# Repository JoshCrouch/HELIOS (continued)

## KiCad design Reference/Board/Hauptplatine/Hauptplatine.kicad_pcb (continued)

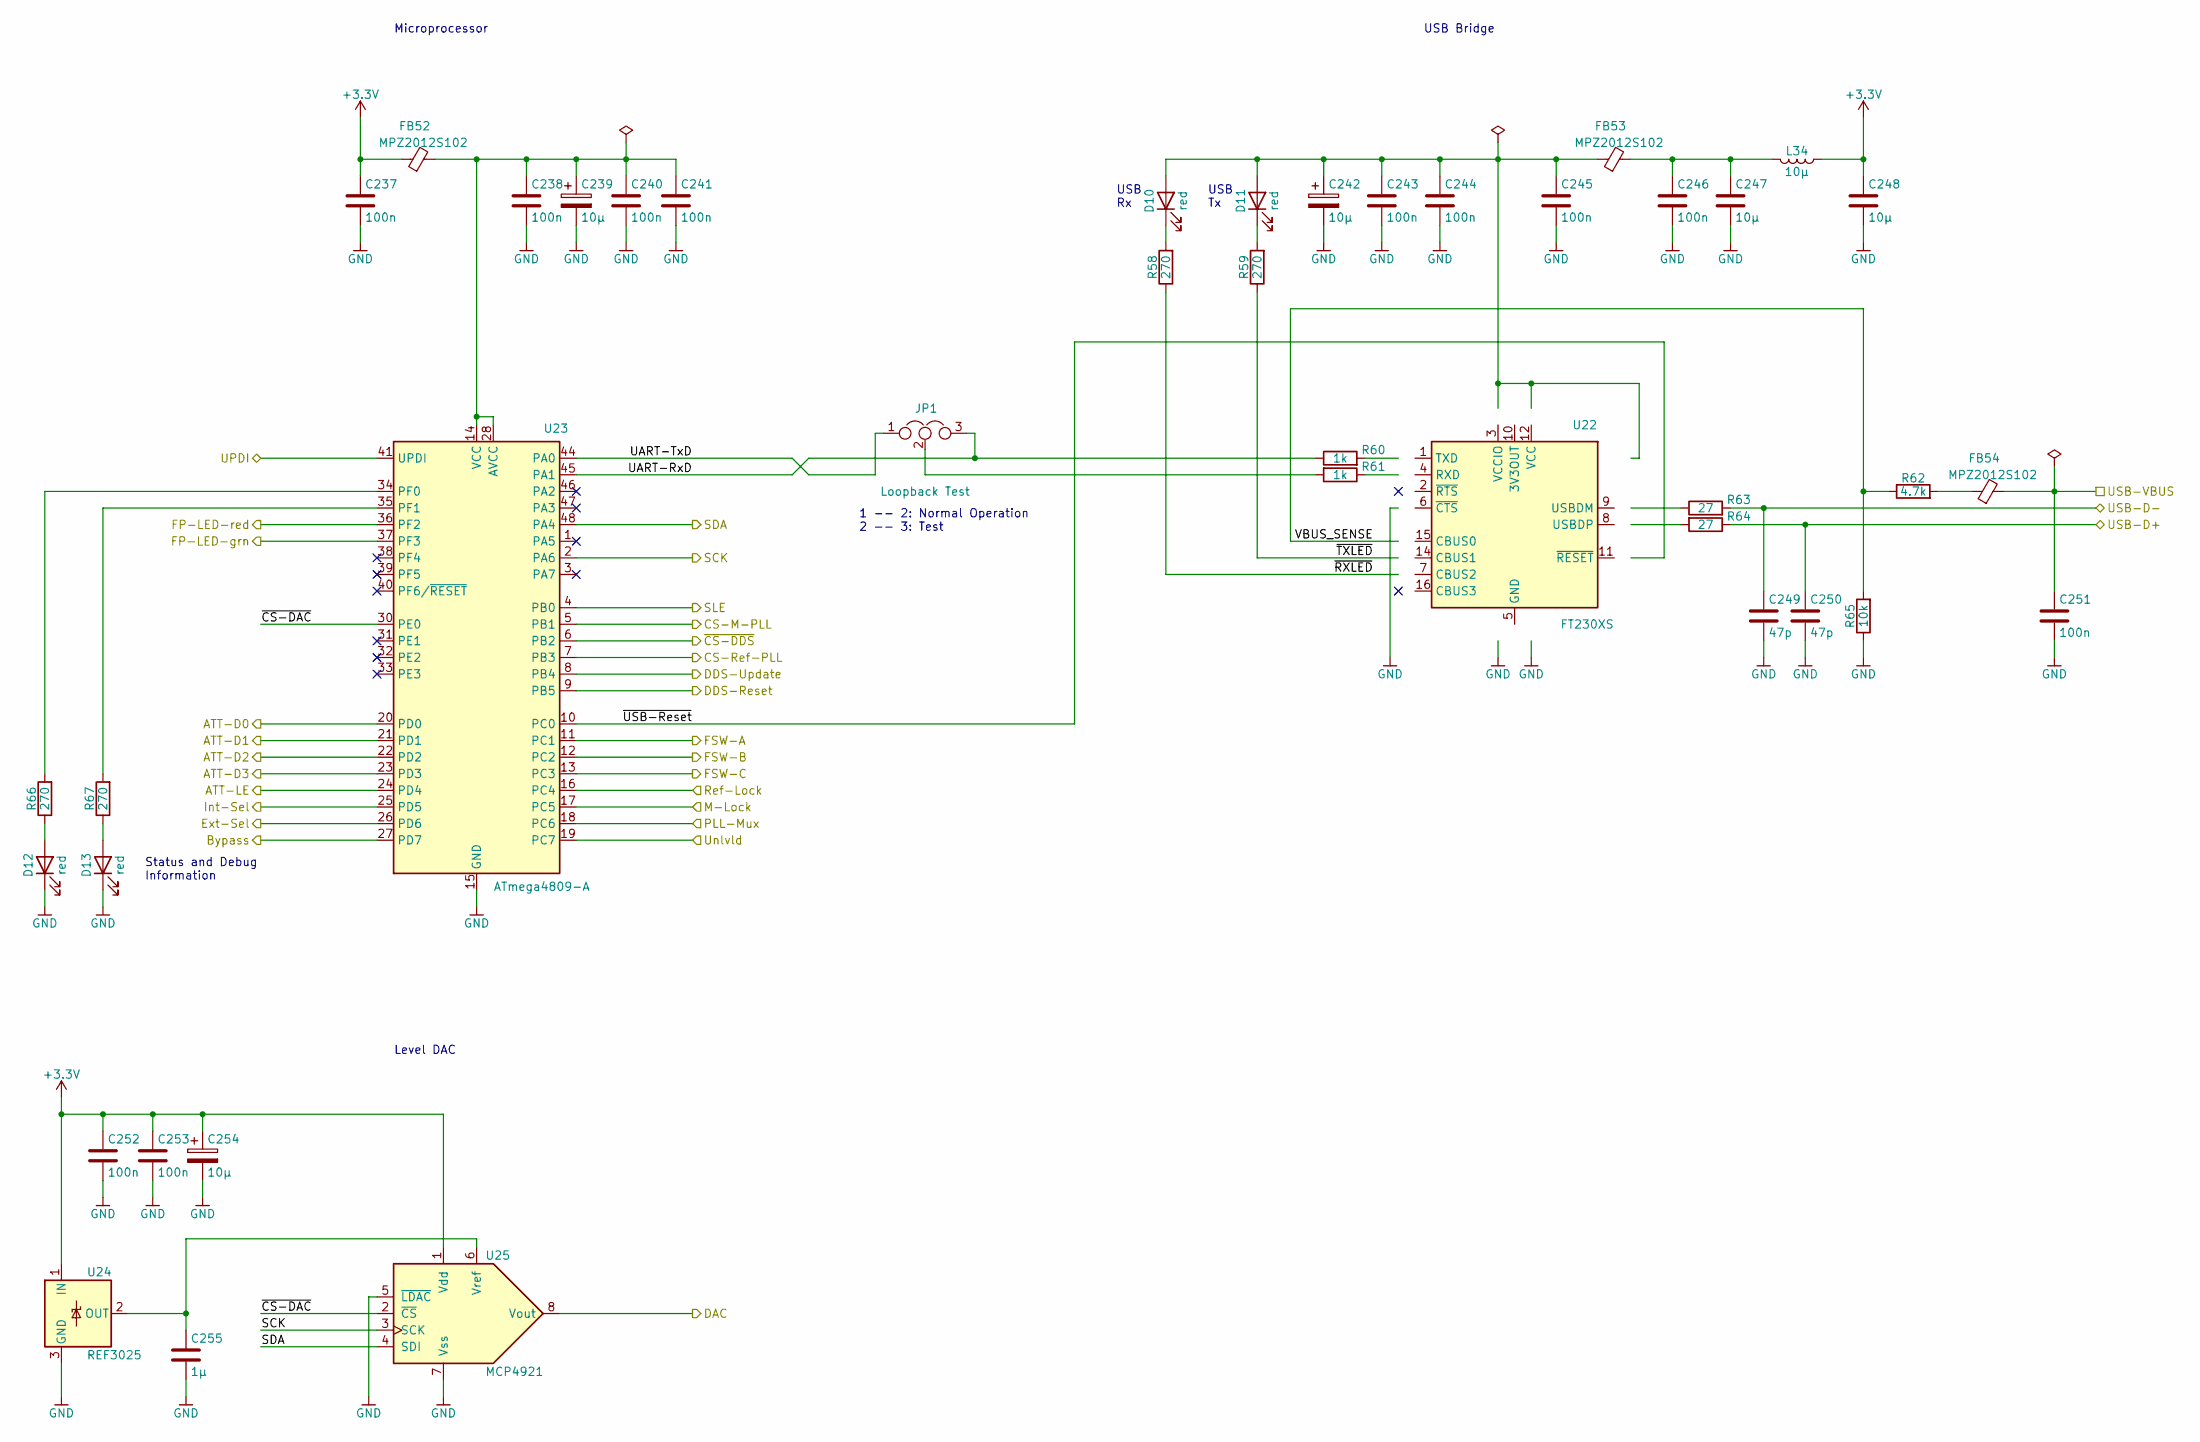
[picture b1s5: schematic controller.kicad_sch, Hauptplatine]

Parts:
C237, C238, C243, C244, C245, C246, C251, C252, C253: 100n; C_0805_2012Metric
C239, C242, C254: 10µ; CP_EIA-3528-21_Kemet-B
C240, C241: 100n; C_0603_1608Metric
C247, C248: 10µ; C_0805_2012Metric
C249, C250: 47p; C_0805_2012Metric
C255: 1µ; C_0805_2012Metric
D10, D11, D12, D13: red; LED_0805_2012Metric
FB52, FB53, FB54: MPZ2012S102; L_0805_2012Metric
JP1: Jumper-3; PinHeader_1x03_P2.54mm_Vertical
L34: 10µ; L_0805_2012Metric
R58, R59, R66, R67: 270; R_0805_2012Metric
R60, R61: 1k; R_0805_2012Metric
R62: 4.7k; R_0805_2012Metric
R63, R64: 27; R_0805_2012Metric
R65: 10k; R_0805_2012Metric
U22: FT230XS; SSOP-16_3.9x4.9mm_P0.635mm
U23: ATmega4809-A; TQFP-48_7x7mm_P0.5mm
U24: REF3025; SOT-23
U25: MCP4921; SOIC-8_3.9x4.9mm_P1.27mm

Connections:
/ATT-D0: U23.20 (PD0); also elsewhere on the board
/ATT-D1: U23.21 (PD1); also elsewhere on the board
/ATT-D2: U23.22 (PD2); also elsewhere on the board
/ATT-D3: U23.23 (PD3); also elsewhere on the board
/ATT-LE: U23.24 (PD4); also elsewhere on the board
/Bypass: U23.27 (PD7); also elsewhere on the board
/CS-M-PLL: U23.5 (PB1); also elsewhere on the board
/CS-Ref-PLL: U23.7 (PB3); also elsewhere on the board
/Controller/DAC: U25.8 (Vout); also elsewhere on the board
/Controller/FP-LED-grn: U23.37 (PF3); also elsewhere on the board
/Controller/FP-LED-red: U23.36 (PF2); also elsewhere on the board
/Controller/UART-RxD: JP1.3, R60.1, U23.45 (PA1)
/Controller/UART-TxD: JP1.1, U23.44 (PA0)
/Controller/UPDI: U23.41 (UPDI); also elsewhere on the board
/Controller/USB-D+: C250.1, R64.1; also elsewhere on the board
/Controller/USB-D-: C249.1, R63.2; also elsewhere on the board
/Controller/USB-VBUS: C251.1, FB54.2; also elsewhere on the board
/Controller/VBUS_SENSE: R62.1, R65.2, U22.15 (CBUS0)
/Controller/~CS-DAC: U23.30 (PE0), U25.2 (~CS)
/Controller/~RXLED: R58.1, U22.7 (CBUS2)
/Controller/~TXLED: R59.1, U22.14 (CBUS1)
/Controller/~USB-Reset: U22.11 (~RESET), U23.10 (PC0)
/DDS-Reset: U23.9 (PB5); also elsewhere on the board
/DDS-Update: U23.8 (PB4); also elsewhere on the board
/Ext-Sel: U23.26 (PD6); also elsewhere on the board
/FSW-A: U23.11 (PC1); also elsewhere on the board
/FSW-B: U23.12 (PC2); also elsewhere on the board
/FSW-C: U23.13 (PC3); also elsewhere on the board
/Int-Sel: U23.25 (PD5); also elsewhere on the board
/M-Lock: U23.17 (PC5); also elsewhere on the board
/PLL-Mux: U23.18 (PC6); also elsewhere on the board
/Ref-Lock: U23.16 (PC4); also elsewhere on the board
/SCK: U23.2 (PA6), U25.3 (SCK); also elsewhere on the board
/SDA: U23.48 (PA4), U25.4 (SDI); also elsewhere on the board
/SLE: U23.4 (PB0); also elsewhere on the board
/Unlvld: U23.19 (PC7); also elsewhere on the board
/~CS-DDS: U23.6 (PB2); also elsewhere on the board
unnamed: C238.1, C239.1, C240.1, C241.1, FB52.2, U23.14 (VCC), U23.28 (AVCC), U23.42 (VCC)
unnamed: C246.1, C247.1, FB53.2, L34.2
unnamed: C255.1, U24.2 (OUT), U25.6 (Vref)
unnamed: D10.1 (K), R58.2
unnamed: D11.1 (K), R59.2
unnamed: D12.2 (A), R66.1
unnamed: D13.2 (A), R67.1
unnamed: FB54.1, R62.2
unnamed: JP1.2, R61.2
unnamed: R60.2, U22.1 (TXD)
unnamed: R61.1, U22.4 (RXD)
unnamed: R63.1, U22.9 (USBDM)
unnamed: R64.2, U22.8 (USBDP)
unnamed: R66.2, U23.34 (PF0)
unnamed: R67.2, U23.35 (PF1)

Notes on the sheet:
1 -- 2: Normal Operation 2 -- 3: Test
Level DAC
Status and Debug Information
USB Tx
USB Rx
USB Bridge
Microprocessor

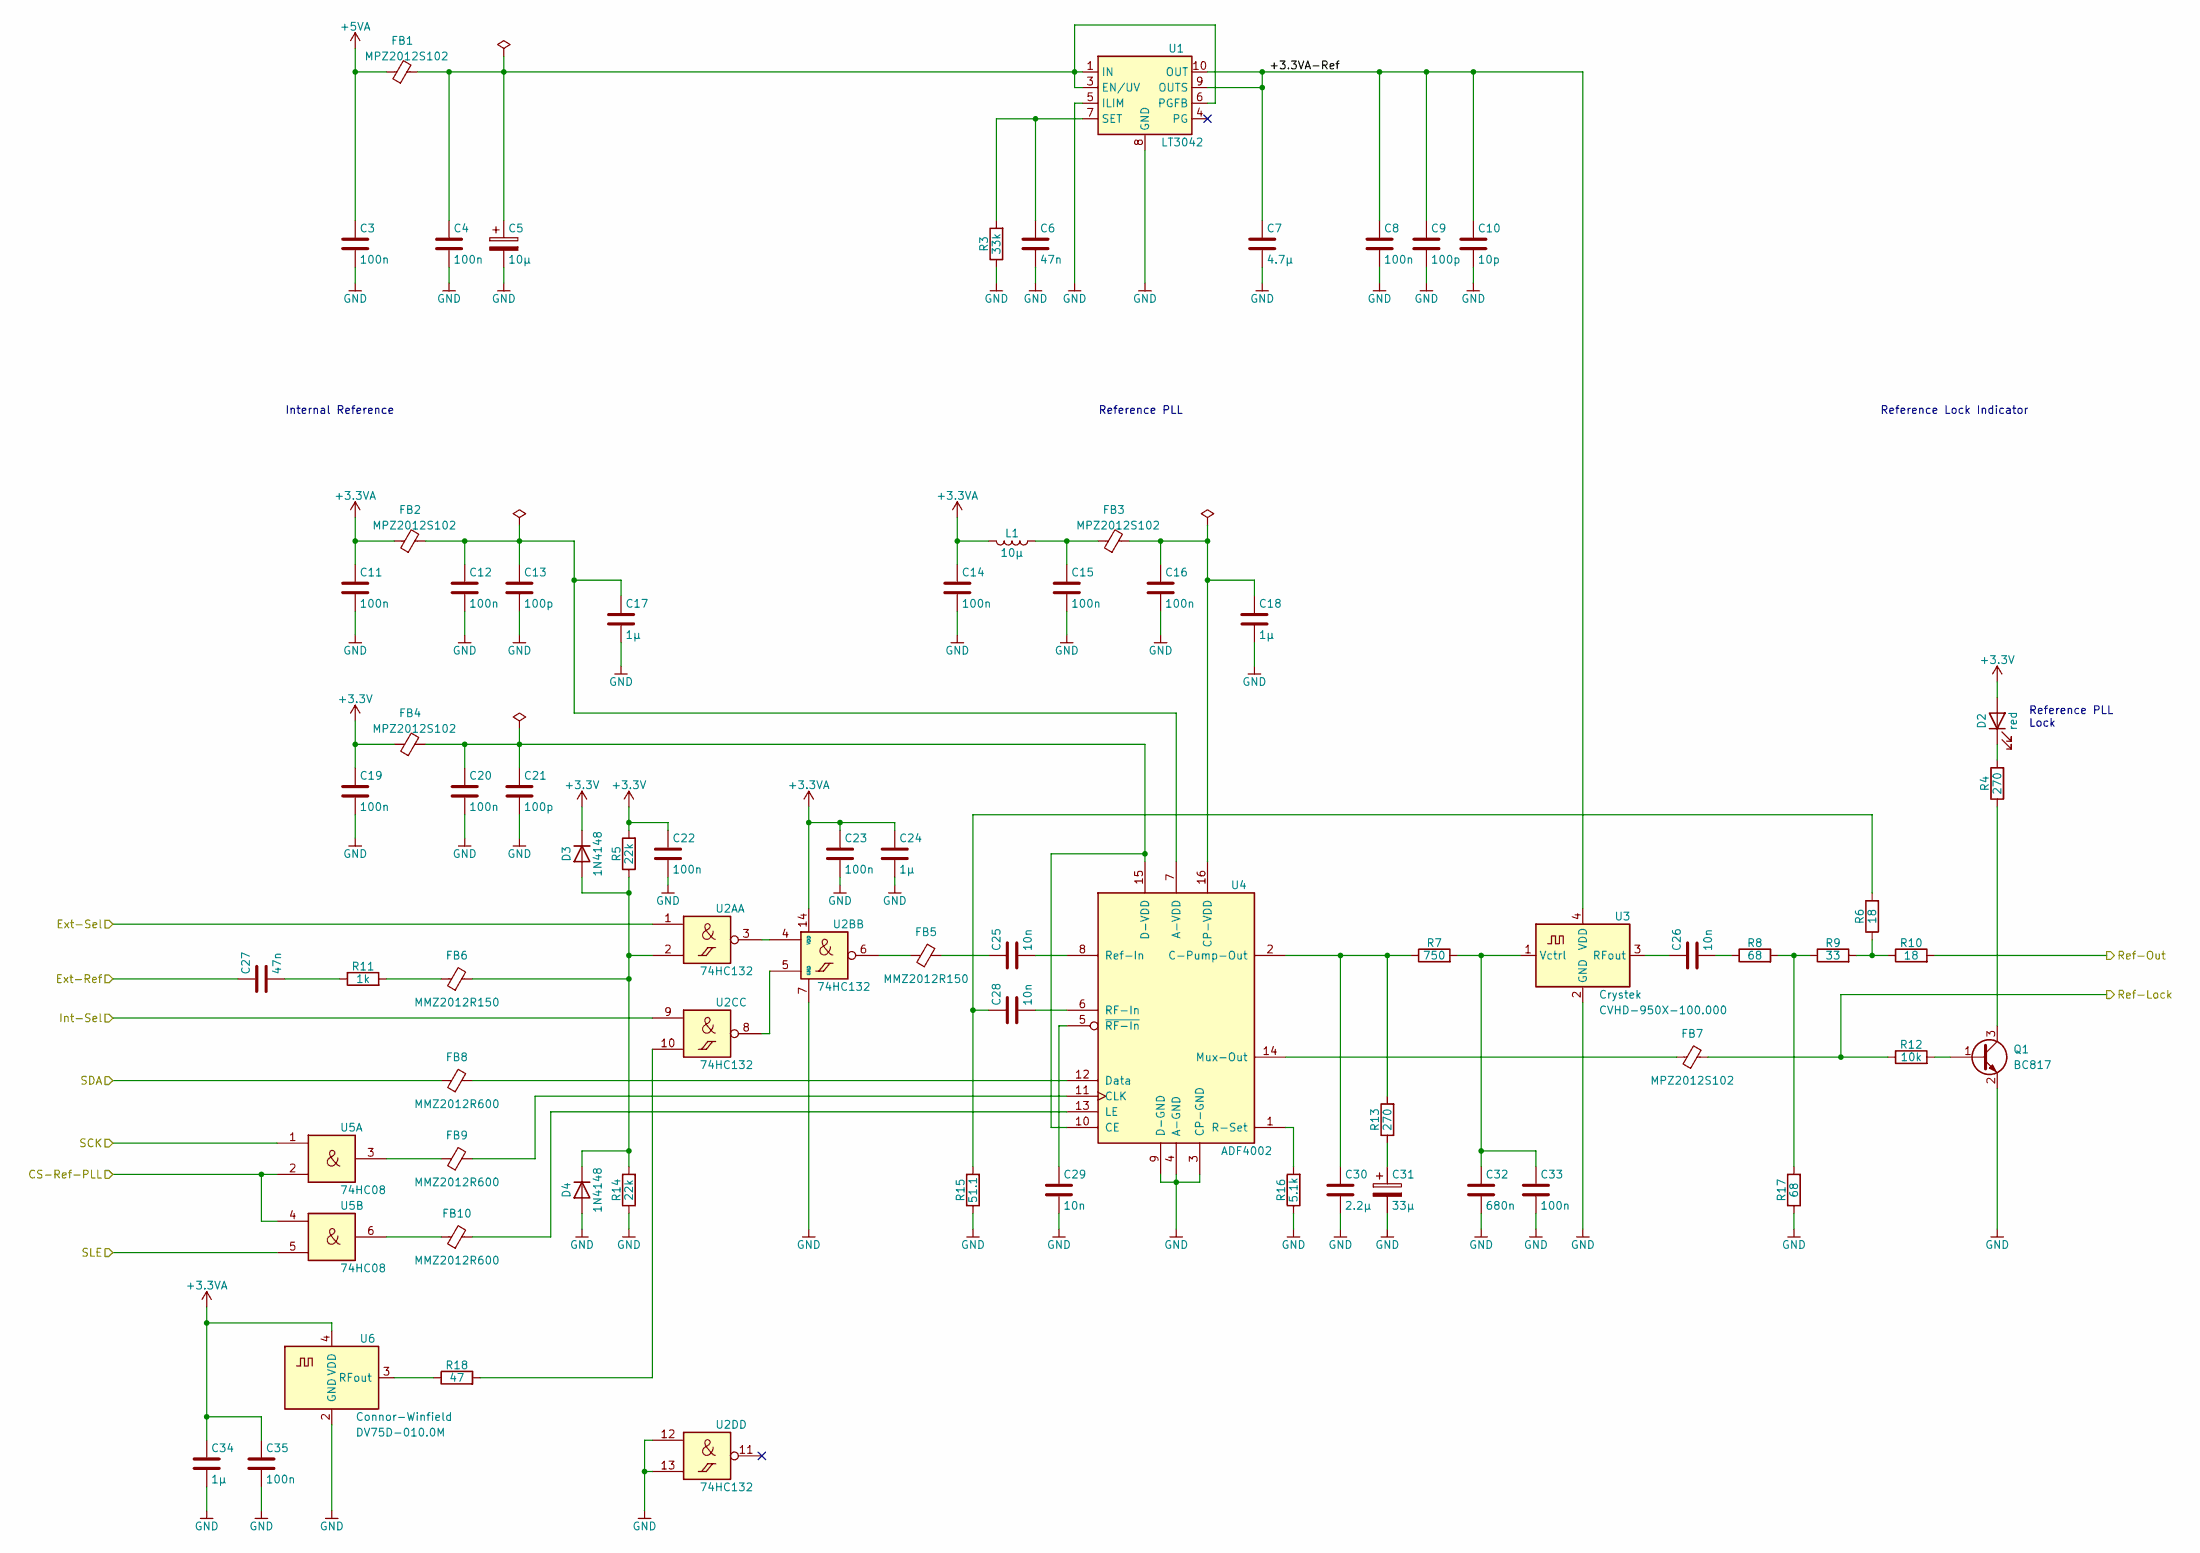
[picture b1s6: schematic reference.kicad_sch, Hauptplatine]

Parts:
C3, C4, C8, C11, C12, C14, C15, C16, C19, C20, C22, C23, C33, C35: 100n; C_0805_2012Metric
C5: 10µ; CP_EIA-3528-21_Kemet-B
C6, C27: 47n; C_0805_2012Metric
C7: 4.7µ; C_0805_2012Metric
C9, C13, C21: 100p; C_0805_2012Metric
C10: 10p; C_0805_2012Metric
C17, C18, C24, C34: 1µ; C_0805_2012Metric
C25, C26, C28, C29: 10n; C_0805_2012Metric
C30: 2.2µ; C_0805_2012Metric
C31: 33µ; CP_Radial_D5.0mm_P2.00mm
C32: 680n; C_0805_2012Metric
D2: red; LED_0805_2012Metric
D3, D4: 1N4148; D_SOD-323F
FB1, FB2, FB3, FB4, FB7: MPZ2012S102; L_0805_2012Metric
FB5, FB6: MMZ2012R150; L_0805_2012Metric
FB8, FB9, FB10: MMZ2012R600; L_0805_2012Metric
L1: 10µ; L_0805_2012Metric
Q1: BC817; SOT-23
R3: 33k; R_0805_2012Metric
R4, R13: 270; R_0805_2012Metric
R5, R14: 22k; R_0805_2012Metric
R6, R10: 18; R_0805_2012Metric
R7: 750; R_0805_2012Metric
R8, R17: 68; R_0805_2012Metric
R9: 33; R_0805_2012Metric
R11: 1k; R_0805_2012Metric
R12: 10k; R_0805_2012Metric
R15: 51.1; R_0805_2012Metric
R16: 5.1k; R_0805_2012Metric
R18: 47; R_0805_2012Metric
U1: LT3042; MSOP-10-1EP_3x3mm_P0.5mm_EP1.68x1.88mm
U2A, U2B, U2C, U2D, U2E: 74HC132; SOIC-14_3.9x8.7mm_P1.27mm
U3: CVHD-950X-100.000; VCXO_CVHD950_Crystek
U4: ADF4002; TSSOP-16_4.4x5mm_P0.65mm
U5: 74HC08; SOIC-14_3.9x8.7mm_P1.27mm
U6: DV75D-010.0M; DV75D_Oscillator_Connor-Winfield

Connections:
+3.3VA: C11.1, C14.1, C23.1, C24.1, C34.1, C35.1, FB2.1, L1.2, U2E.14 (VDD), U6.4 (VDD); also elsewhere on the board
+5VA: C3.1, FB1.1; also elsewhere on the board
/CS-Ref-PLL: U5.2, U5.4; also elsewhere on the board
/PLL and DDS/Ref-In: R10.2; also elsewhere on the board
/Ref-Lock: FB7.2, R12.1; also elsewhere on the board
/Reference/+3.3VA-Ref: C7.1, C8.1, C9.1, C10.1, U1.9 (OUTS), U1.10 (OUT), U3.4 (VDD)
/Reference/Ext-Ref: C27.1; also elsewhere on the board
/SCK: U5.1; also elsewhere on the board
/SDA: FB8.1; also elsewhere on the board
/SLE: U5.5; also elsewhere on the board
unnamed: C4.1, C5.1, FB1.2, U1.1 (IN), U1.2 (IN), U1.3 (EN/UV), U1.6 (PGFB)
unnamed: C6.1, R3.2, U1.7 (SET)
unnamed: C12.1, C13.1, C17.1, FB2.2, U4.7 (A-VDD)
unnamed: C15.1, FB3.1, L1.1
unnamed: C16.1, C18.1, FB3.2, U4.16 (CP-VDD)
unnamed: C20.1, C21.1, FB4.2, U4.10 (CE), U4.15 (D-VDD)
unnamed: C25.1, FB5.2
unnamed: C25.2, U4.8 (Ref-In)
unnamed: C26.1, U3.3 (RFout)
unnamed: C26.2, R8.1
unnamed: C27.2, R11.1
unnamed: C28.1, R6.2, R15.2
unnamed: C28.2, U4.6 (RF-In)
unnamed: C29.1, U4.5 (~RF-In)
unnamed: C30.1, R7.1, R13.2, U4.2 (C-Pump-Out)
unnamed: C31.1, R13.1
unnamed: C32.1, C33.1, R7.2, U3.1 (Vctrl)
unnamed: D2.1 (K), R4.2
unnamed 202: D3.2 (A), D4.1 (K), FB6.2, R5.1, R14.2, U2A.2; also elsewhere on the board
unnamed 215: FB5.1, U2B.6; also elsewhere on the board
unnamed: FB6.1, R11.2
unnamed: FB7.1, U4.14 (Mux-Out)
unnamed: FB8.2, U4.12 (Data)
unnamed: FB9.1, U5.3
unnamed: FB9.2, U4.11 (CLK)
unnamed: FB10.1, U5.6
unnamed: FB10.2, U4.13 (LE)
unnamed: Q1.1 (B), R12.2
unnamed: Q1.3 (C), R4.1
unnamed: R6.1, R9.2, R10.1
unnamed: R16.2, U4.1 (R-Set)
unnamed: R8.2, R9.1, R17.2
unnamed: R18.1, U6.3 (RFout)
unnamed 254: R18.2, U2C.10; also elsewhere on the board
unnamed: U2A.3, U2B.4
unnamed: U2B.5, U2C.8

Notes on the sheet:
Reference PLL
Reference Lock Indicator
Internal Reference
Reference PLL Lock

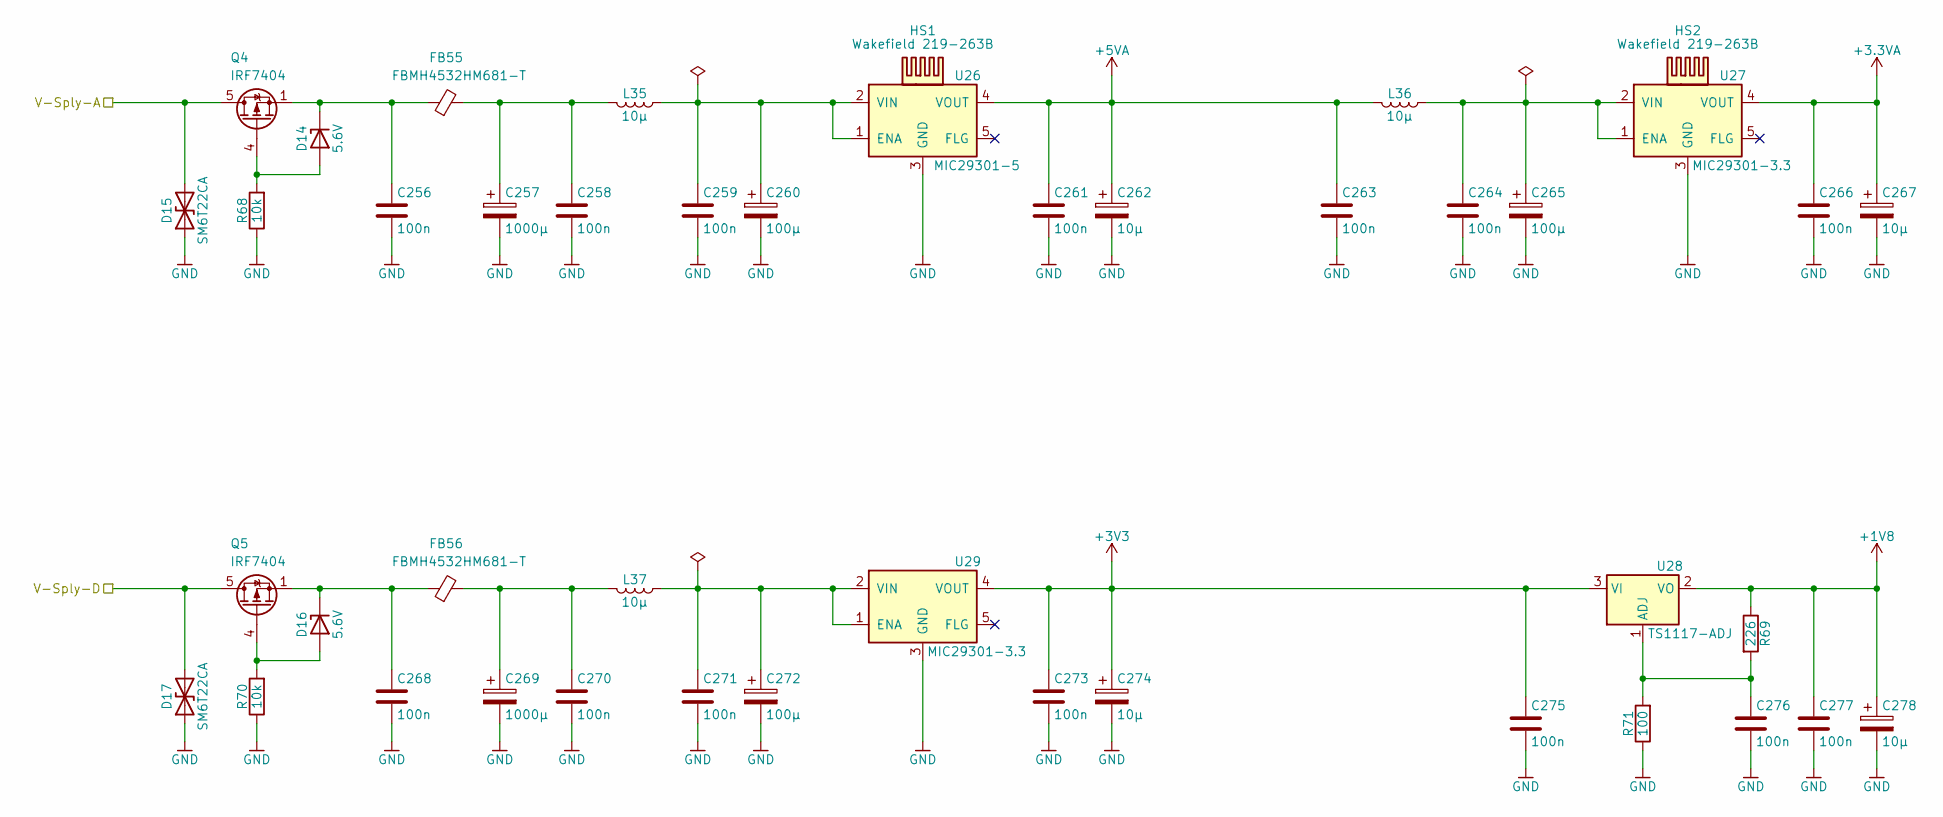
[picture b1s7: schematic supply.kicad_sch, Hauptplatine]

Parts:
C256, C258, C259, C261, C263, C264, C266, C268, C270, C271, C273, C275, C276, C277: 100n; C_0805_2012Metric
C257, C269: 1000µ; CP_Radial_D10.0mm_P5.00mm
C260, C265, C272: 100µ; CP_Radial_D6.3mm_P2.50mm
C262, C267, C274, C278: 10µ; CP_Radial_D5.0mm_P2.00mm
D14, D16: 5.6V; D_SOD-123
D15, D17: SM6T22CA; D_SMB
FB55, FB56: FBMH4532HM681-T; L_1812_4532Metric
HS1, HS2: Wakefield 219-263B; Heatsink-TO263_219-263B-TR_Wakefield
L35, L37: 10µ; L_Wuerth_WE-PD-Typ-LS
L36: 10µ; Wuerth_WE-TPC_Shielded
Q4, Q5: IRF7404; SOIC-8_3.9x4.9mm_P1.27mm
R68, R70: 10k; R_0805_2012Metric
R69: 226; R_0805_2012Metric
R71: 100; R_0805_2012Metric
U26: MIC29301-5; TO-263-5_TabPin3
U27, U29: MIC29301-3.3; TO-263-5_TabPin3
U28: TS1117-ADJ; TO-252-3_TabPin2

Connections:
+1V8: C277.1, C278.1, R69.1, U28.2 (VO); also elsewhere on the board
+3.3VA: C266.1, C267.1, U27.4 (VOUT); also elsewhere on the board
+5VA: C261.1, C262.1, C263.1, L36.2, U26.4 (VOUT); also elsewhere on the board
/Power Supply/V-Sply-A: D15.2 (A2), D17.2 (A2), Q4.5 (D), Q4.6 (D), Q4.7 (D), Q4.8 (D), Q5.5 (D), Q5.6 (D), Q5.7 (D), Q5.8 (D); also elsewhere on the board
unnamed: C256.1, D14.1 (K), FB55.1, Q4.1 (S), Q4.2 (S), Q4.3 (S)
unnamed: C257.1, C258.1, FB55.2, L35.2
unnamed: C259.1, C260.1, L35.1, U26.1 (ENA), U26.2 (VIN)
unnamed: C264.1, C265.1, L36.1, U27.1 (ENA), U27.2 (VIN)
unnamed: C268.1, D16.1 (K), FB56.1, Q5.1 (S), Q5.2 (S), Q5.3 (S)
unnamed: C269.1, C270.1, FB56.2, L37.2
unnamed: C271.1, C272.1, L37.1, U29.1 (ENA), U29.2 (VIN)
unnamed: C276.1, R69.2, R71.2, U28.1 (ADJ)
unnamed: D14.2 (A), Q4.4 (G), R68.2
unnamed: D16.2 (A), Q5.4 (G), R70.2

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
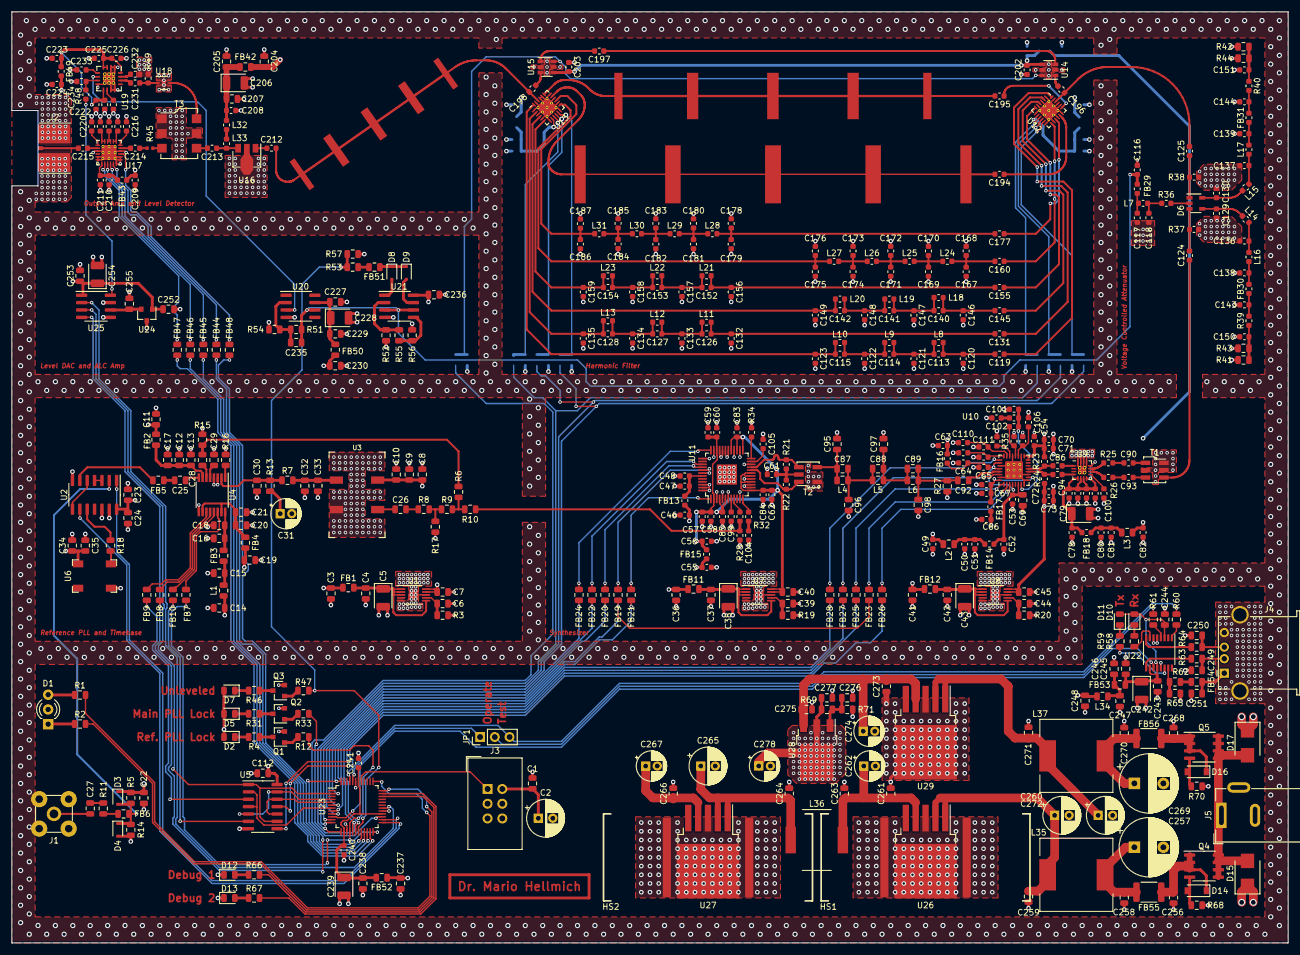
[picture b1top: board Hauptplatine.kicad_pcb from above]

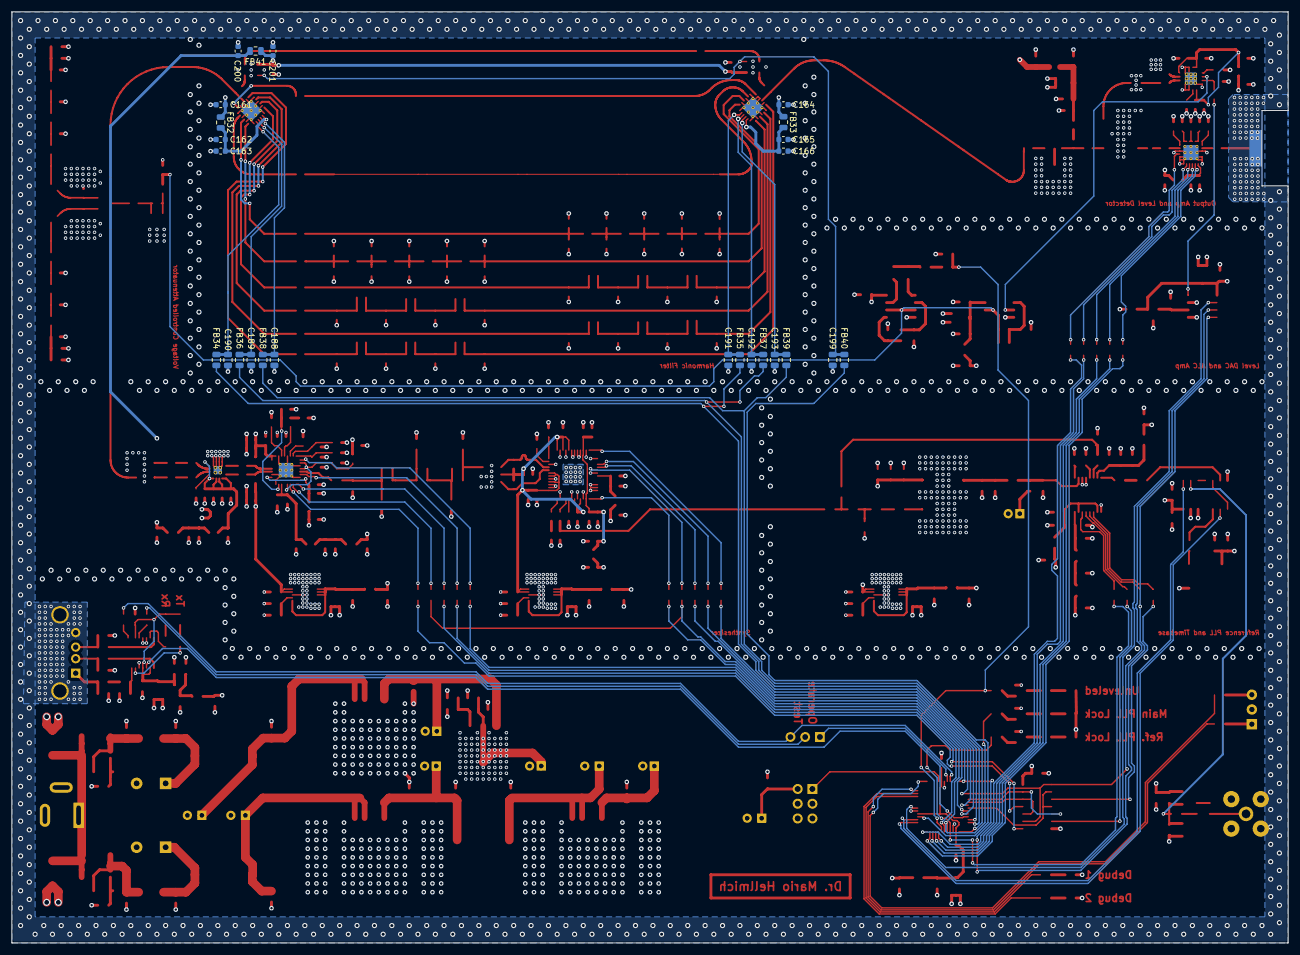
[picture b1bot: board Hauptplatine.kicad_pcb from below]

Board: 4 copper layers, 220.0 x 160.5 mm, 531 parts (25 on the bottom side), 280 nets.

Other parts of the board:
U2: 74HC132; SOIC-14_3.9x8.7mm_P1.27mm
U21: TLC272; SOIC-8_3.9x4.9mm_P1.27mm

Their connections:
+3.3VA: U2.14; also elsewhere on the board
+5VA: U21.8; also elsewhere on the board
/Ext-Sel: U2.1; also elsewhere on the board
/Harmonic Filter/Level-Ctrl: U21.3, U21.6; also elsewhere on the board
/Int-Sel: U2.9; also elsewhere on the board
unnamed 202: U2.2; also elsewhere on the board
unnamed 207: U21.1; also elsewhere on the board
unnamed 208: U21.7; also elsewhere on the board
unnamed 215: U2.6; also elsewhere on the board
unnamed 254: U2.10; also elsewhere on the board
unnamed 264: U21.2; also elsewhere on the board
unnamed 265: U21.5; also elsewhere on the board
unnamed: U2.3, U2.4
unnamed: U2.5, U2.8

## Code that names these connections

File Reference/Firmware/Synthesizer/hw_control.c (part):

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
// Define pin number bit masks for hardware connected to the controller
// Chip enable, reset and update lines:
#define SLE					PIN0_bm
#define MPLL_CS				PIN1_bm
#define	DDS_CS				PIN2_bm
#define REFPLL_CS			PIN3_bm
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#define REFPLL_LOCK			PIN4_bm
#define MPLL_LOCK			PIN5_bm
#define MPLL_MUX			PIN6_bm
#define UNLVLD				PIN7_bm

// Status LEDs
#define STSLED_1			PIN0_bm
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#define REFPLL_PORT			PORTB
#define DAC_PORT			PORTE
#define HFILTER_PORT		PORTC															// Harmonic filter
#define BYPASS_PORT			PORTD															// Bypass switch for harmonic filter
#define ATTEN_PORT			PORTD
#define SPI_PORT			PORTB															// Chip select lines
#define REFSEL_PORT			PORTD															// Reference mode selection lines
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#define DESELECT_ATTEN		ATTEN_PORT.OUTCLR  = ATTEN_LE

// Define LE select and de-select macros
#define SELECT_LE			SPI_PORT.OUTSET = SLE
#define DESELECT_LE			SPI_PORT.OUTCLR = SLE

// Define DDS I/O-Update macro
#define SELECT_DDSUPDT		DDS_PORT.OUTSET = DDS_UPDATE
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
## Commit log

2025-12-29 Init Commit
2026-01-01 LO Loop Filter + Sims
